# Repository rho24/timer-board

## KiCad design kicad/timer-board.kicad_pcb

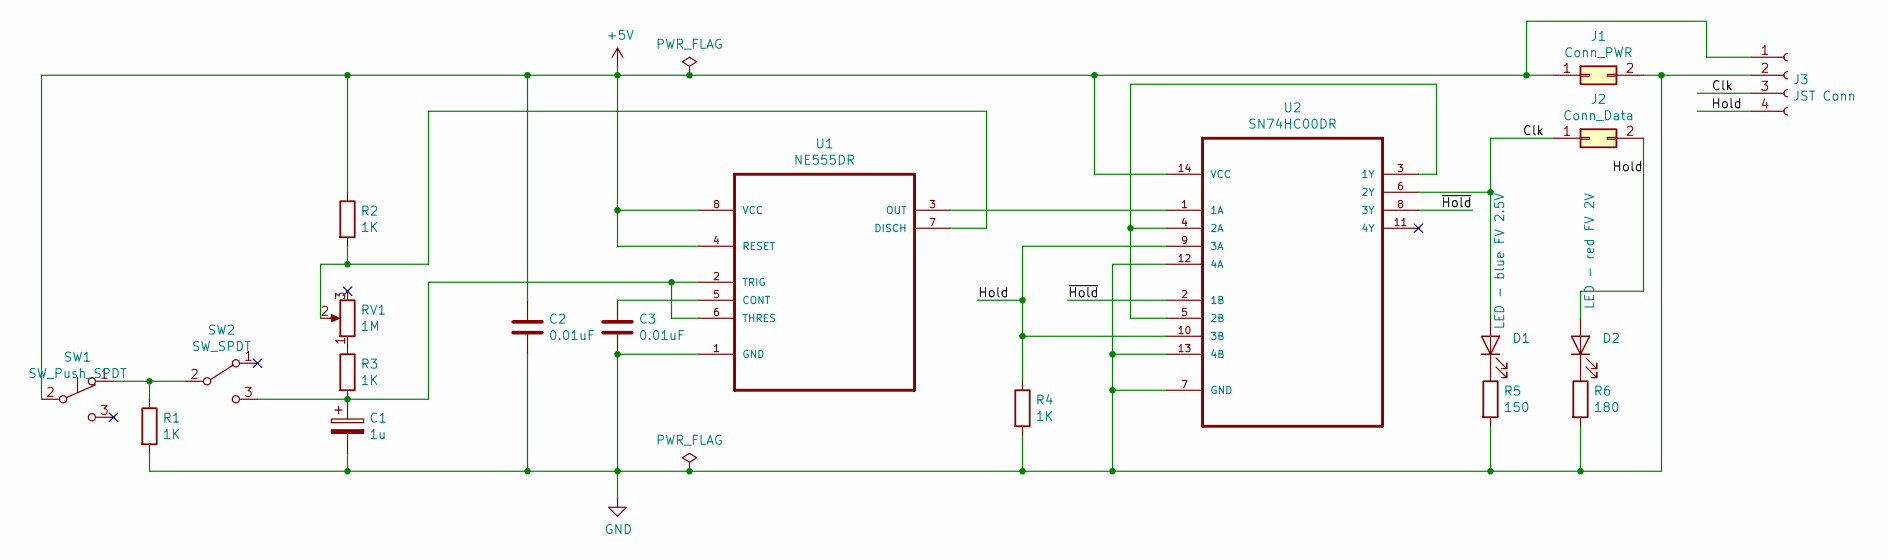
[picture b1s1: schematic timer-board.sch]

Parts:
C1: 1u; C_0603_1608Metric; LCSC C15849
C2, C3: 0.01uF; C_0603_1608Metric; LCSC C57112
D1: LED - blue FV 2.5V; LED_0603_1608Metric; LCSC C72041
D2: LED - red FV 2V; LED_0603_1608Metric; LCSC C2286
J1: Conn_PWR; PinHeader_2x01_P2.54mm_Vertical
J2: Conn_Data; PinHeader_2x01_P2.54mm_Vertical
J3: JST Conn; JST_XH_B4B-XH-AM_1x04_P2.50mm_Vertical
R1, R2, R3, R4: 1K; R_0603_1608Metric; LCSC C21190
R5: 150; R_0603_1608Metric; LCSC C22808
R6: 180; R_0603_1608Metric; LCSC C22828
RV1: 1M; 6mm_trimmer
SW1: SW_Push_SPDT; switch_push_spdt
SW2: SW_SPDT; switch_toggle_spdt
U1: NE555DR; SOIC127P600X175-8N; LCSC C7593
U2: SN74HC00DR; SOIC127P600X175-14N; LCSC C10090

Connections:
+5V: C2.1, J1.1, J3.1, R2.1, SW1.2 (B), U1.4 (RESET), U1.8 (VCC), U2.14 (VCC)
/Clk: D1.2 (A), J2.1, J3.3, U2.6 (2Y)
/Hold: D2.2 (A), J2.2, J3.4, R4.1, U2.9 (3A), U2.10 (3B)
/~Hold~: U2.2 (1B), U2.8 (3Y)
GND: C1.2, C2.2, C3.2, J1.2, J3.2, R1.2, R4.2, R5.2, R6.2, U1.1 (GND), U2.7 (GND), U2.12 (4A), U2.13 (4B)
unnamed: C1.1, R3.2, SW2.3 (C), U1.2 (TRIG), U1.6 (THRES)
unnamed: C3.1, U1.5 (CONT)
unnamed: D1.1 (K), R5.1
unnamed: D2.1 (K), R6.1
unnamed: R1.1, SW1.1 (A), SW2.2 (B)
unnamed: R2.2, RV1.2, U1.7 (DISCH)
unnamed: R3.1, RV1.1
unnamed: U1.3 (OUT), U2.1 (1A)
unnamed: U2.3 (1Y), U2.4 (2A), U2.5 (2B)

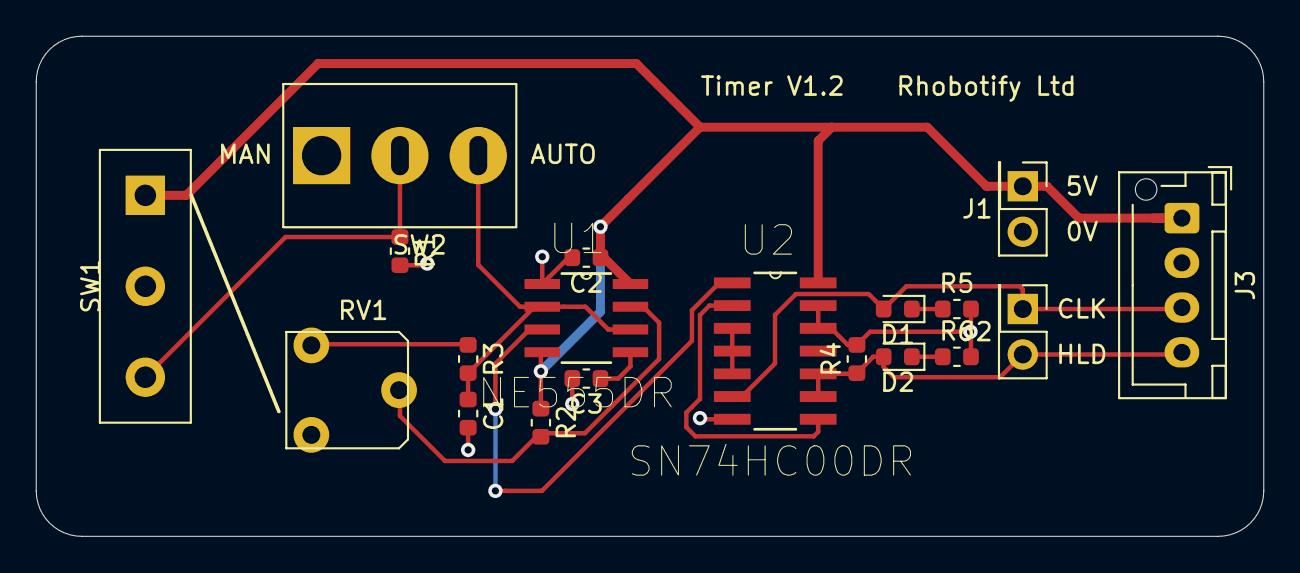
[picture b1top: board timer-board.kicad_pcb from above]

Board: 2 copper layers, 68.6 x 27.9 mm, 19 parts (0 on the bottom side), 14 nets.

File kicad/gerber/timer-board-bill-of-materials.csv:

Comment,Designator,Footprint, LCSC
1u,C1,Capacitor_SMD:C_0603_1608Metric,C15849
0.01uF,"C3,C2",Capacitor_SMD:C_0603_1608Metric,C57112
LED - blue FV 2.5V,D1,LED_SMD:LED_0603_1608Metric,C72041
LED - red FV 2V,D2,LED_SMD:LED_0603_1608Metric,C2286
Conn_PWR,J1,Connector_PinHeader_2.54mm:PinHeader_2x01_P2.54mm_Vertical,
Conn_Data,J2,Connector_PinHeader_2.54mm:PinHeader_2x01_P2.54mm_Vertical,
JST Conn,J3,Connector_JST:JST_XH_B4B-XH-AM_1x04_P2.50mm_Vertical,
1K,"R3,R2,R1,R4",Resistor_SMD:R_0603_1608Metric,C21190
150,R5,Resistor_SMD:R_0603_1608Metric,C22808
180,R6,Resistor_SMD:R_0603_1608Metric,C22828
1M,RV1,mine:6mm_trimmer,
SW_Push_SPDT,SW1,mine:switch_push_spdt,
SW_SPDT,SW2,mine:switch_toggle_spdt,
NE555DR,U1,SOIC127P600X175-8N,C7593
SN74HC00DR,U2,SOIC127P600X175-14N,C10090

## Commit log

2019-10-14 First stab
2019-10-15 Rework
2019-10-15 tracks with errors
2019-10-15 Text
2019-10-26 Add templates
2019-10-26 Add libs
2019-10-26 More work
2019-10-27 Fix rules
2019-10-28 Round corners
2019-10-29 Add holes
2019-10-29 Thicken VCC
2019-10-29 Add gerber
2019-10-29 Fix holes
2019-10-29 Add bill of materials etc
2019-10-30 Version 1.1
2019-10-30 Some cache
2019-11-02 Update pot footprint
2019-11-02 Version 1.2
